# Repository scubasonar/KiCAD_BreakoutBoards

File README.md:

# KiCAD_BreakoutBoards
Various breakout boards for ICs I like

S6AE101A_solar_harvester - 

"The S6AE101A is a power management IC (PMIC) for energy harvesting that is built into circuits of solar cells connected in series, output power control circuits, output capacitor storage circuits, and power switching circuits of primary batteries. Super-low-power operation is possible using a consumption current of only 250 nA and startup power of only 1.2 μW. As a result, even slight amounts of power generation can be obtained from compact solar cells under low-brightness environments of approximately 100 lx."

LTC3110_supercap_backup - 

"The LTC3110EFE#PBF is a bidirectional buck-boost DC to DC regulator with capacitor charger and balancer in 24 pin TSSOP package. Its wide 0.1V to 5.5V capacitor/battery voltage and 1.8V to 5.25V system backup voltage ranges make it well suited to wide variety of backup applications using super capacitors or batteries. A proprietary low noise switching algorithm optimizes efficiency with capacitor/battery voltages that are above, below or equal to system output voltage. The LTC3110 can autonomously perform transition from charge to backup mode or switch modes based on an external command. Pin selectable burst mode operation reduces standby current and improves light load efficiency which combined with 1μA shutdown current make the LTC3110 ideally suited for backup applications. The device also includes voltage supervisors for direction control and end of charge, general purpose comparator with open collector output for interfacing with microcontroller."

as7265x_color_sensors - 

"The 18-channel 3-chip calibrated visible through near-infrared chipset is ideal for emerging spectral sensing applications such as horticulture, fluid quality/spectral component analysis and complex spectral identification, including anti-counterfeiting and authentication. Today’s announcement brings the new 2017 offerings from the AS726x multispectral sensing products to 4 unique solution sets, including 6-channel visible, near-IR, true color and 18-channel family members.

The AS7265x chipset consists of 3 highly integrated 6-channel sensor devices, each only 4.5 x 4.4 x 2.5mm, in efficient land-grid array packages with integrated apertures. The master-slave-slave architecture appears as a single logical device, simplifying system integration and decreasing time to market. The 18-channels span wavelengths from 410 to 940nm with 20nm filter widths."

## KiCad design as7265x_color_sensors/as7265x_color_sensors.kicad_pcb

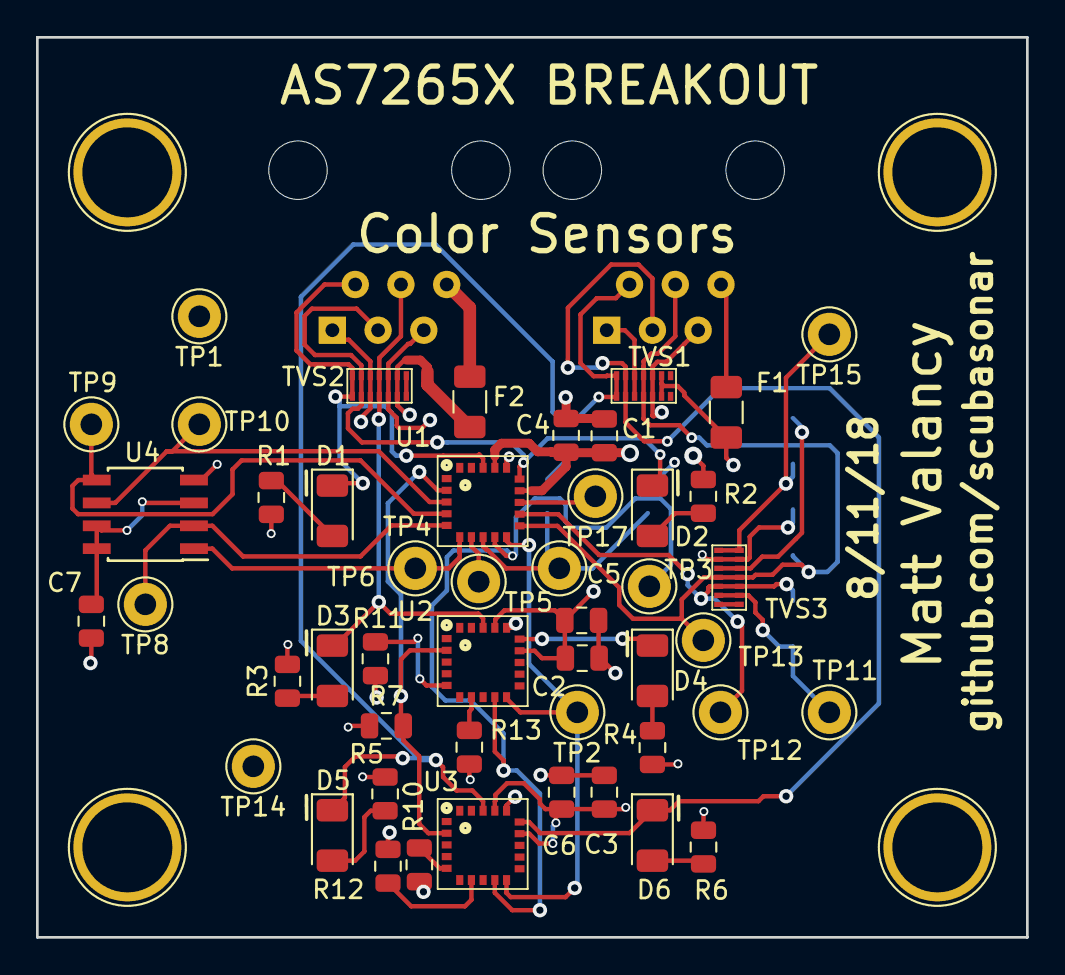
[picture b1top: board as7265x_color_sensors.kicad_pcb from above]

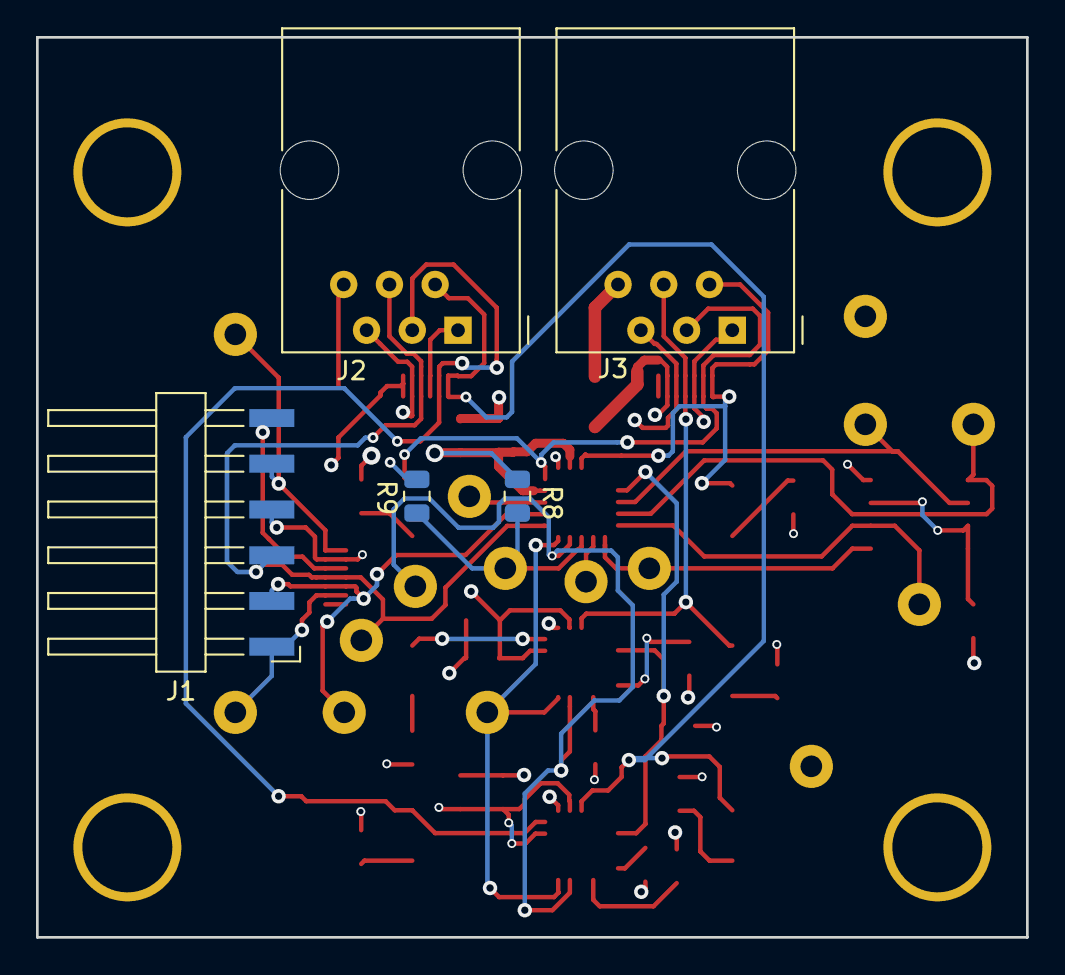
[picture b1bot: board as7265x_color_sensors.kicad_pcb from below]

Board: 4 copper layers, 55.0 x 50.0 mm, 53 parts (5 on the bottom side), 34 nets.

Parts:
C1, C2, C3: 100nF; C_0805_2012Metric
C4, C5, C6: 10uF; C_0805_2012Metric
C7: 1uF; C_0805_2012Metric
D1, D2, D3, D4, D5, D6: LED_Small; LED_1206_3216Metric
F1, F2: Polyfuse; C_1206_3216Metric
J1: Conn_01x06_Male; Harwin_M20-89006xx_1x06_P2.54mm_Horizontal
J2, J3: RJ12; RJ12_Amphenol_54601
R1, R2, R3, R4, R5, R6: R_Small; R_0805_2012Metric
R7: 10k; R_0805_2012Metric
R8: DNP; R_0805_2012Metric
R9: 0R; R_0805_2012Metric
R10, R11, R12, R13: 10K; R_0805_2012Metric
TP1, TP2, TP3, TP4, TP5, TP6, TP8, TP9, TP10, TP11, TP12, TP13, TP14, TP15, TP17: TestPoint; Pin_D1.0mm_L10.0mm_LooseFit
TVS1, TVS2, TVS3: SP3012-06UTG; uDFN-14_3.5x1.35x0.5mm
U1: AS72651; LGA-20_4.5mm_4.7mm_2.5mm
U2: AS72652; LGA-20_4.5mm_4.7mm_2.5mm
U3: AS72653; LGA-20_4.5mm_4.7mm_2.5mm
U4: AT25SF041; SOIC-8_3.9x4.9mm_P1.27mm

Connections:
+3V3: C1.1, C2.1, C3.1, C4.1, C5.1, C6.1, C7.1, F1.1, F2.1, J1.4, R1.2, R2.2, R3.2, R4.2, R5.2, R6.2, R7.1, R8.2, TP1.1, TP14.1, TVS1.13, TVS2.13, TVS3.9, U1.14, U1.17, U2.14, U2.17, U3.14, U3.17, U4.3, U4.7, U4.8
/CTS: J1.5, TP15.1, TVS3.8
/DTR: J1.1, TP11.1, TVS3.13
/LED1: D1.1, J3.2, TVS2.8, U1.18
/LED2: D2.1, J3.3, TVS2.9, U1.15
/LED3: D3.1, J3.4, TVS2.11, U2.18
/LED4: D4.1, J3.5, TVS2.12, U2.15
/LED5: D5.1, J2.2, TVS1.8, U3.18
/LED6: D6.1, J2.3, TVS1.9, U3.15
/RXI: J1.3, J2.4, TP13.1, TVS1.11, TVS3.11, U1.11
/TXO: J1.2, J2.5, TP12.1, TVS1.12, TVS3.12, U1.12
/~INT: TP17.1, U1.13
GND: C1.2, C2.2, C3.2, C4.2, C5.2, C6.2, C7.2, J1.6, J2.1, J3.1, R9.1, R10.1, R11.1, R12.1, R13.1, TVS1.10, TVS2.10, TVS3.10, U1.16, U2.16, U3.16, U4.4
unnamed: D1.2, R1.1
unnamed: D2.2, R2.1
unnamed: D3.2, R3.1
unnamed: D4.2, R4.1
unnamed: D5.2, R5.1
unnamed: D6.2, R6.1
unnamed: F1.2, J2.6
unnamed: F2.2, J3.6
unnamed: R7.2, U1.2, U2.2, U3.2
unnamed: R8.1, R9.2, TP5.1, U1.8
unnamed: R10.2, U3.5
unnamed: R11.2, U2.5
unnamed: R12.2, U3.7
unnamed: R13.2, U2.7
unnamed: TP2.1, U1.10, U2.10, U3.10
unnamed: TP3.1, U1.9, U2.9, U3.9
unnamed: TP4.1, U1.7
unnamed: TP6.1, U1.6, U4.1
unnamed: TP8.1, U1.5, U4.2
unnamed: TP9.1, U1.4, U4.5
unnamed: TP10.1, U1.3, U4.6

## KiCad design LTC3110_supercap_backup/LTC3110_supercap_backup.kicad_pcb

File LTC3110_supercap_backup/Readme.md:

Solar powered energy harvesting board with large super capacitor based storage for garden lights or other long life devices. 

Schematic: https://github.com/scubasonar/KiCAD_BreakoutBoards/blob/master/LTC3110_supercap_backup/Images/LTC3110_supercap_backup.sch.svg

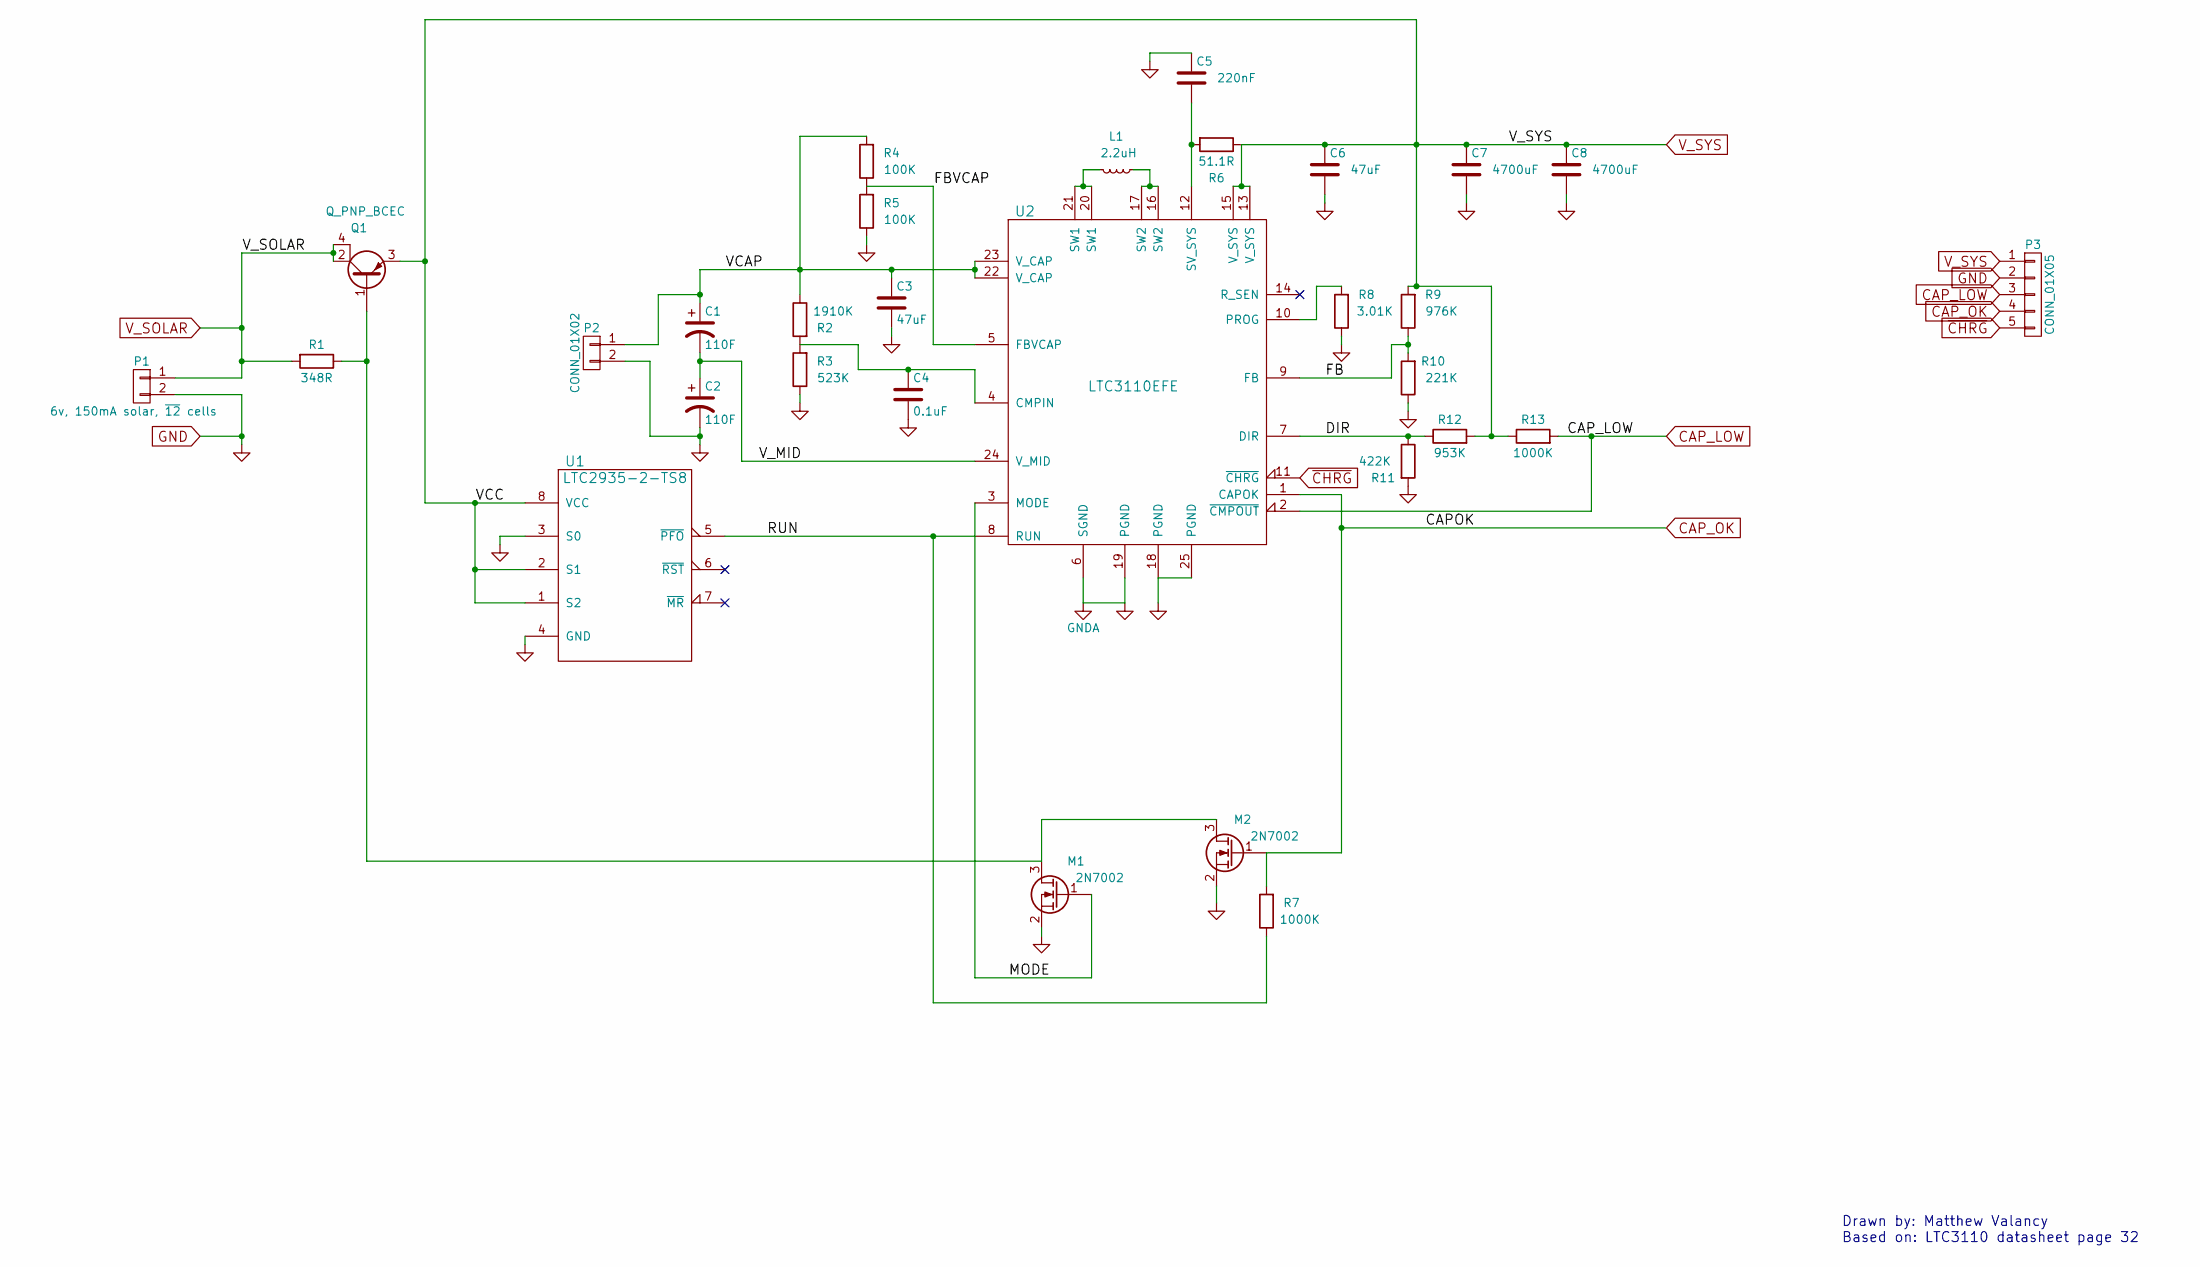
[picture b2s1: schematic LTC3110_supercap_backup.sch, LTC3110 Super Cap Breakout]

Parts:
C1, C2: 110F; Cap_HB1860; MFG_PN HB1860-2R5117-R
C3, C6: 47uF; C_0805_HandSoldering
C4: 0.1uF; C_0805_HandSoldering
C5: 220nF; C_0805_HandSoldering
C7, C8: 4700uF; C_Rect_L32_W15_P27; MFG_PN UHW1E472MHD
L1: 2.2uH; SMD_IND_CLF7045; MFG_PN CLF7045T-2R2N-D
M1, M2: 2N7002; SOT-23
P1: 6v, 150mA solar, ~12 cells; Pin_Header_Straight_1x02
P2: CONN_01X02; Pin_Header_Straight_1x02
P3: CONN_01X05; Pin_Header_Straight_1x05
Q1: Q_PNP_BCEC; SOT-223; MFG_PN PBSS302
R1: 348R; R_0805_HandSoldering
R2: 1910K; R_0805_HandSoldering; MFG_PN ERJ-6ENF1914V
R3: 523K; R_0805_HandSoldering; MFG_PN CRCW0805523KFKEA
R4, R5: 100K; R_0805_HandSoldering
R6: 51.1R; R_0805_HandSoldering
R7, R13: 1000K; R_0805_HandSoldering
R8: 3.01K; R_0805_HandSoldering
R9: 976K; R_0805_HandSoldering
R10: 221K; R_0805_HandSoldering
R11: 422K; R_0805_HandSoldering
R12: 953K; R_0805_HandSoldering
U1: LTC2935-2-TS8; TSOT-23-8
U2: LTC3110EFE; TSSOP-24

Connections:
/DIR: R11.1, R12.1, U2.7 (DIR)
/FB: R9.1, R10.2, U2.9 (FB)
/FBVCAP: R4.1, R5.2, U2.5 (FBVCAP)
/MODE: M1.1 (G), U2.3 (MODE)
/RUN: R7.1, U1.5 (~PFO), U2.8 (RUN)
/VCAP: C1.1, C3.1, P2.1, R2.1, R4.2, U2.22 (V_CAP), U2.23 (V_CAP)
/V_MID: C1.2, C2.1, U2.24 (V_MID)
CAP_LOW: P3.3, R13.2, U2.2 (~CMPOUT)
CAP_OK: M2.1 (G), P3.4, R7.2, U2.1 (CAPOK)
GND: C2.2, C3.2, C4.2, C5.1, C6.2, C7.2, C8.2, M1.2 (S), M2.2 (S), P1.2, P2.2, P3.2, R3.1, R5.1, R8.1, R10.1, R11.2, U1.3 (S0), U1.4 (GND), U2.6 (SGND), U2.18 (PGND), U2.19 (PGND), U2.25 (PGND)
unnamed: C4.1, R2.2, R3.2, U2.4 (CMPIN)
unnamed: C5.2, R6.2, U2.12 (SV_SYS)
unnamed: L1.1, U2.16 (SW2), U2.17 (SW2)
unnamed: L1.2, U2.20 (SW1), U2.21 (SW1)
unnamed: M1.3 (D), M2.3 (D), Q1.1 (B), R1.1
unnamed: R8.2, U2.10 (PROG)
V_SOLAR: P1.1, Q1.2 (C), Q1.4 (C), R1.2
V_SYS: C6.1, C7.1, C8.1, P3.1, Q1.3 (E), R6.1, R9.2, R12.2, R13.1, U1.1 (S2), U1.2 (S1), U1.8 (VCC), U2.13 (V_SYS), U2.15 (V_SYS)
~CHRG: P3.5, U2.11 (~CHRG)

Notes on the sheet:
Drawn by: Matthew Valancy Based on: LTC3110 datasheet page 32

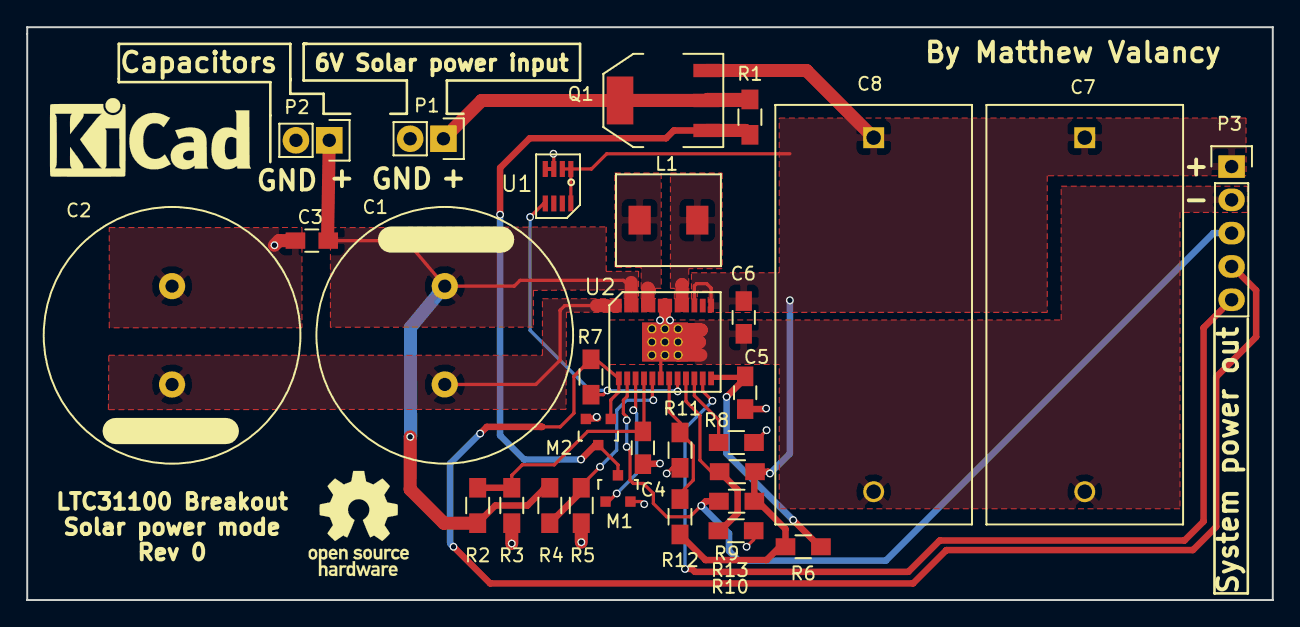
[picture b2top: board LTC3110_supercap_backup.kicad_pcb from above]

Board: 2 copper layers, 95.0 x 43.7 mm, 30 parts (0 on the bottom side), 19 nets.

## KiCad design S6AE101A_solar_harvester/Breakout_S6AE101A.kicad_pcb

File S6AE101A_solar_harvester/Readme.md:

Energy harvester for low power solar, needs very little power to start up and not a lot of solar cells.

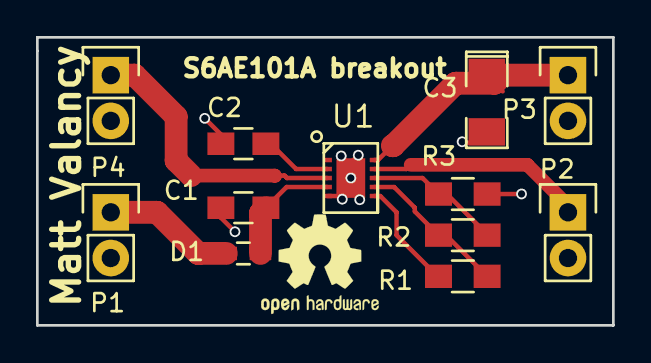
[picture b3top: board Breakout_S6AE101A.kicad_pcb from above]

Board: 2 copper layers, 32.0 x 16.0 mm, 12 parts (0 on the bottom side), 10 nets.

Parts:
C1: 10uF; C_0805_HandSoldering
C2: 1uF; C_0805_HandSoldering
C3: CP1; SMD-1206_Pol
D1: D_Schottky; C_0603_HandSoldering
P1, P2, P3, P4: CONN_01X02; Pin_Header_Straight_1x02
R1, R2, R3: R; R_0805_HandSoldering
U1: S6AE101A; VNE-010

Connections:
/SET_FB: R1.1, U1.6
/SET_H: R1.2, R2.1, U1.7
/SET_L: R2.2, R3.1, U1.8
/VBAT: P4.1, U1.3
/VDD: C1.1, D1.1, U1.4
/VINT: C2.1, U1.2
/VOUT: P2.1, U1.9
/VSOL: D1.2, P1.1
/VSTOR: C3.1, P3.1, U1.10
GNDA: C1.2, C2.2, C3.2, P1.2, P2.2, P3.2, P4.2, R3.2, U1.0, U1.5

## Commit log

2016-08-31 added S6AE101A PCB
2016-08-31 Removed junk files
2016-08-31 added documents for LTC3110
2016-08-31 Update README.md
    added chip descriptions
2016-09-01 Added more data sheets relevant and duplicated demo circuit from main LTC3110 data sheet
2016-09-02 Updated license
2016-09-02 Updated layout to include more net lables, ports, connectors
2016-09-02 Schematic tweaked and annotated, looking good, time for footprint matching and layout.
2016-09-02 saved project
2016-09-04 Selected critical components for LTC3110 breakout, associated footprints and added necessary footprints to library, output netlist and started layout
2016-09-05 Layout almost complete
2016-09-05 re-routed CAP_OK to avoid major ground plane division
2016-09-05 fixed silk screen designator problems and small tweaks to fill areas
2016-09-05 added more silk screen info for debug, board name, etc
2016-09-05 Added images
2017-10-26 start of new project
2017-10-26 Update Readme.md
    zzz
2018-07-29 removed unused folder
2018-08-05 start of new color sensor breakout
2018-08-05 added basic sensor chips with led outputs
2018-08-05 schematic almost done, missing some footprints for the color sensors, place holders used
2018-08-06 chip footprints fixed, started layout
2018-08-06 added more info to schematic
2018-08-06 adding TVS diode arrays
2018-08-07 added test points, more layout progress
2018-08-07 worked on layout
2018-08-11 layout looks just about done
2018-08-11 added pic and gerbers
2018-08-11 made solder mask black in pic
2018-09-06 latest??
